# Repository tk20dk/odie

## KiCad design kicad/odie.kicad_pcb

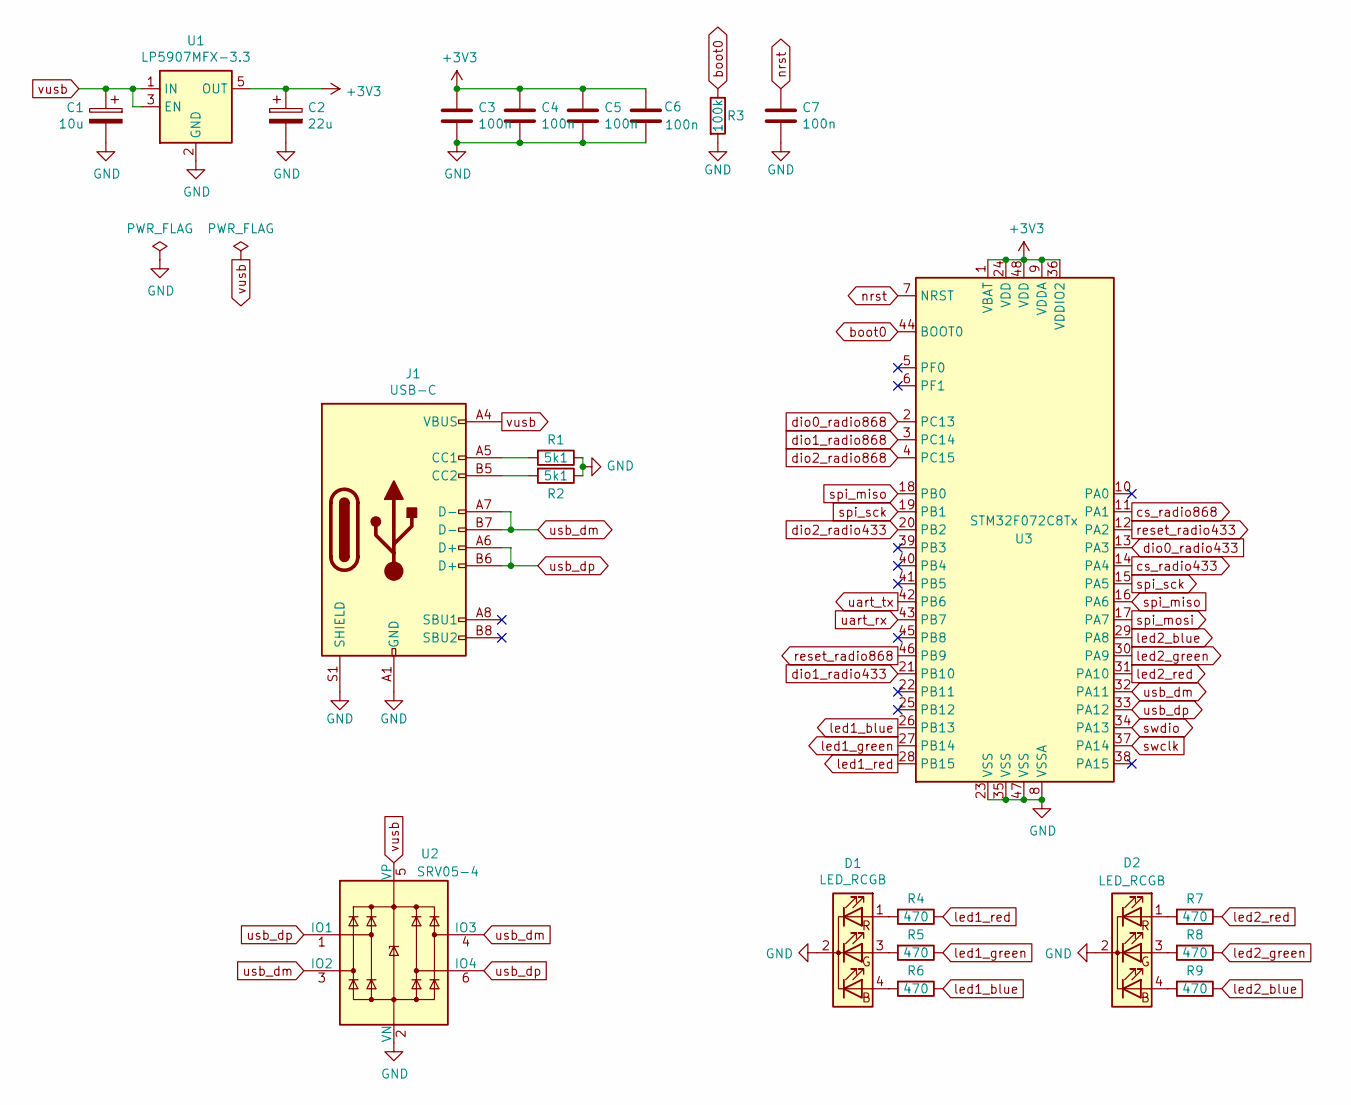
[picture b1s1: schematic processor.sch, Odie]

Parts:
C1: 10u; CP_EIA-3528-12_Kemet-T
C2: 22u; CP_EIA-3528-12_Kemet-T
C3, C4, C5, C6, C7: 100n; C_0603_1608Metric
D1, D2: LED_RCGB; LED_D5.0mm-4
J1: USB-C; USB_C_Receptacle_HRO_TYPE-C-31-M-12
R1, R2: 5k1; R_0603_1608Metric
R3: 100k; R_0603_1608Metric
R4, R5, R6, R7, R8, R9: 470; R_0603_1608Metric
U1: LP5907MFX-3.3; SOT-23-5
U2: SRV05-4; SOT-23-6
U3: STM32F072C8Tx; LQFP-48_7x7mm_P0.5mm

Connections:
GND: C1.2, C2.2, C3.2, C4.2, C5.2, C6.2, C7.2, D1.2 (K), D2.2 (K), J1.A1 (GND), J1.A12 (GND), J1.B1 (GND), J1.B12 (GND), J1.S1 (SHIELD), R1.1, R2.1, R3.2, U1.2 (GND), U2.2 (VN), U3.8 (VSSA), U3.23 (VSS), U3.35 (VSS), U3.47 (VSS); also elsewhere on the board
unnamed: D1.1 (RA), R4.2
unnamed: D1.3 (GA), R5.2
unnamed: D1.4 (BA), R6.2
unnamed: D2.1 (RA), R7.2
unnamed: D2.3 (GA), R8.2
unnamed: D2.4 (BA), R9.2
unnamed: J1.A5 (CC1), R1.2
unnamed: J1.B5 (CC2), R2.2
boot0: R3.1, U3.44 (BOOT0)
cs_radio433: U3.14 (PA4); also elsewhere on the board
cs_radio868: U3.11 (PA1); also elsewhere on the board
dio0_radio433: U3.13 (PA3); also elsewhere on the board
dio0_radio868: U3.2 (PC13); also elsewhere on the board
dio1_radio433: U3.21 (PB10); also elsewhere on the board
dio1_radio868: U3.3 (PC14); also elsewhere on the board
dio2_radio433: U3.20 (PB2); also elsewhere on the board
dio2_radio868: U3.4 (PC15); also elsewhere on the board
led1_blue: R6.1, U3.26 (PB13)
led1_green: R5.1, U3.27 (PB14)
led1_red: R4.1, U3.28 (PB15)
led2_blue: R9.1, U3.29 (PA8)
led2_green: R8.1, U3.30 (PA9)
led2_red: R7.1, U3.31 (PA10)
nrst: C7.1, U3.7 (NRST)
reset_radio433: U3.12 (PA2); also elsewhere on the board
reset_radio868: U3.46 (PB9); also elsewhere on the board
spi_miso: U3.16 (PA6), U3.18 (PB0); also elsewhere on the board
spi_mosi: U3.17 (PA7); also elsewhere on the board
spi_sck: U3.15 (PA5), U3.19 (PB1); also elsewhere on the board
swclk: U3.37 (PA14); also elsewhere on the board
swdio: U3.34 (PA13); also elsewhere on the board
uart_rx: U3.43 (PB7); also elsewhere on the board
uart_tx: U3.42 (PB6); also elsewhere on the board
usb_dm: J1.A7 (D-), J1.B7 (D-), U2.3 (IO2), U2.4 (IO3), U3.32 (PA11)
usb_dp: J1.A6 (D+), J1.B6 (D+), U2.1 (IO1), U2.6 (IO4), U3.33 (PA12)
vusb: C1.1, J1.A4 (VBUS), J1.A9 (VBUS), J1.B4 (VBUS), J1.B9 (VBUS), U1.1 (IN), U1.3 (EN), U2.5 (VP)

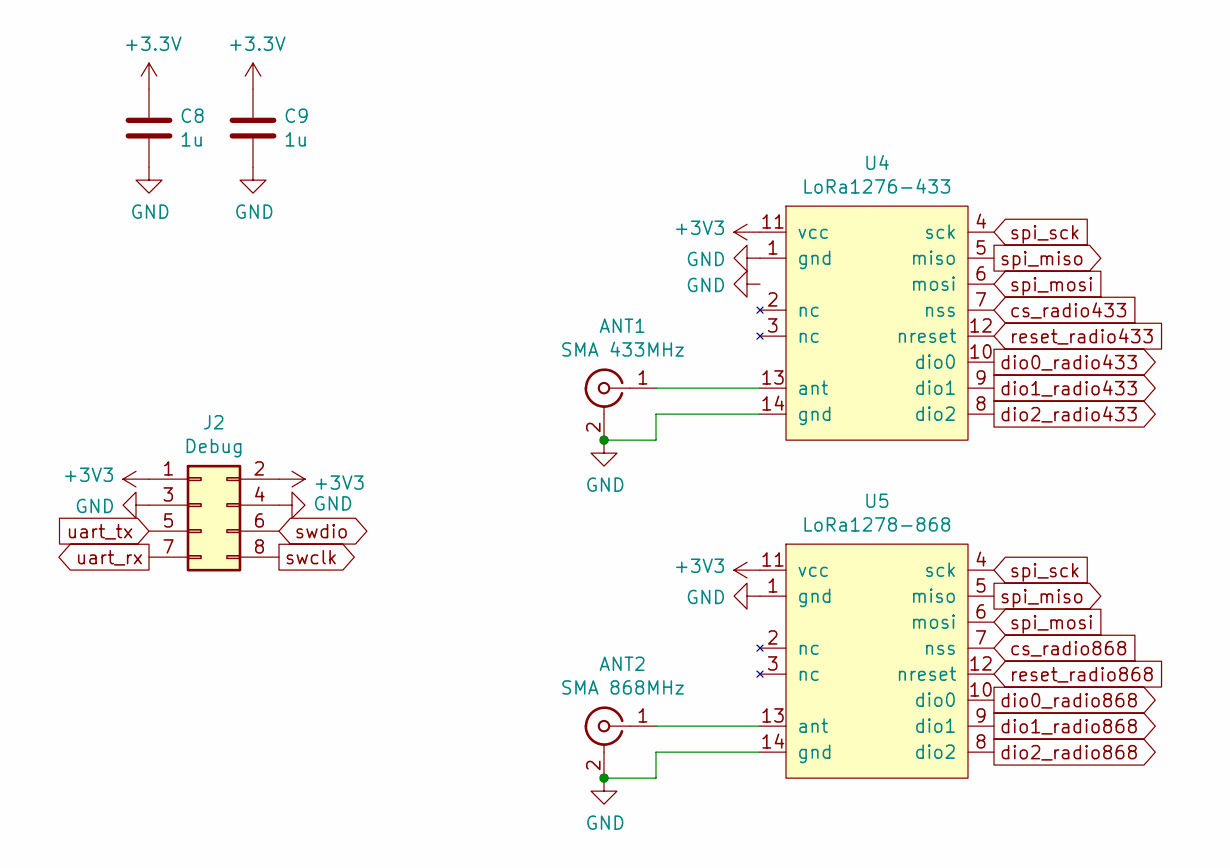
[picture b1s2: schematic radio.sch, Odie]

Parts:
ANT1: SMA 433MHz; SMA_Molex_73251-2200_Horizontal
ANT2: SMA 868MHz; SMA_Molex_73251-2200_Horizontal
C8, C9: 1u; C_0805_2012Metric
J2: Debug; PinHeader_2x04_P2.54mm_Vertical
U4: LoRa1276-433; NicerRF-LoRa1276
U5: LoRa1278-868; NicerRF-LoRa1276

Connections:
GND: ANT1.2 (Ext), ANT2.2 (Ext), C8.2, C9.2, J2.3, J2.4, U4.1 (gnd), U4.14 (gnd), U5.1 (gnd), U5.14 (gnd); also elsewhere on the board
unnamed: ANT1.1 (In), U4.13 (ant)
unnamed: ANT2.1 (In), U5.13 (ant)
cs_radio433: U4.7 (nss); also elsewhere on the board
cs_radio868: U5.7 (nss); also elsewhere on the board
dio0_radio433: U4.10 (dio0); also elsewhere on the board
dio0_radio868: U5.10 (dio0); also elsewhere on the board
dio1_radio433: U4.9 (dio1); also elsewhere on the board
dio1_radio868: U5.9 (dio1); also elsewhere on the board
dio2_radio433: U4.8 (dio2); also elsewhere on the board
dio2_radio868: U5.8 (dio2); also elsewhere on the board
reset_radio433: U4.12 (nreset); also elsewhere on the board
reset_radio868: U5.12 (nreset); also elsewhere on the board
spi_miso: U4.5 (miso), U5.5 (miso); also elsewhere on the board
spi_mosi: U4.6 (mosi), U5.6 (mosi); also elsewhere on the board
spi_sck: U4.4 (sck), U5.4 (sck); also elsewhere on the board
swclk: J2.8; also elsewhere on the board
swdio: J2.6; also elsewhere on the board
uart_rx: J2.7; also elsewhere on the board
uart_tx: J2.5; also elsewhere on the board

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
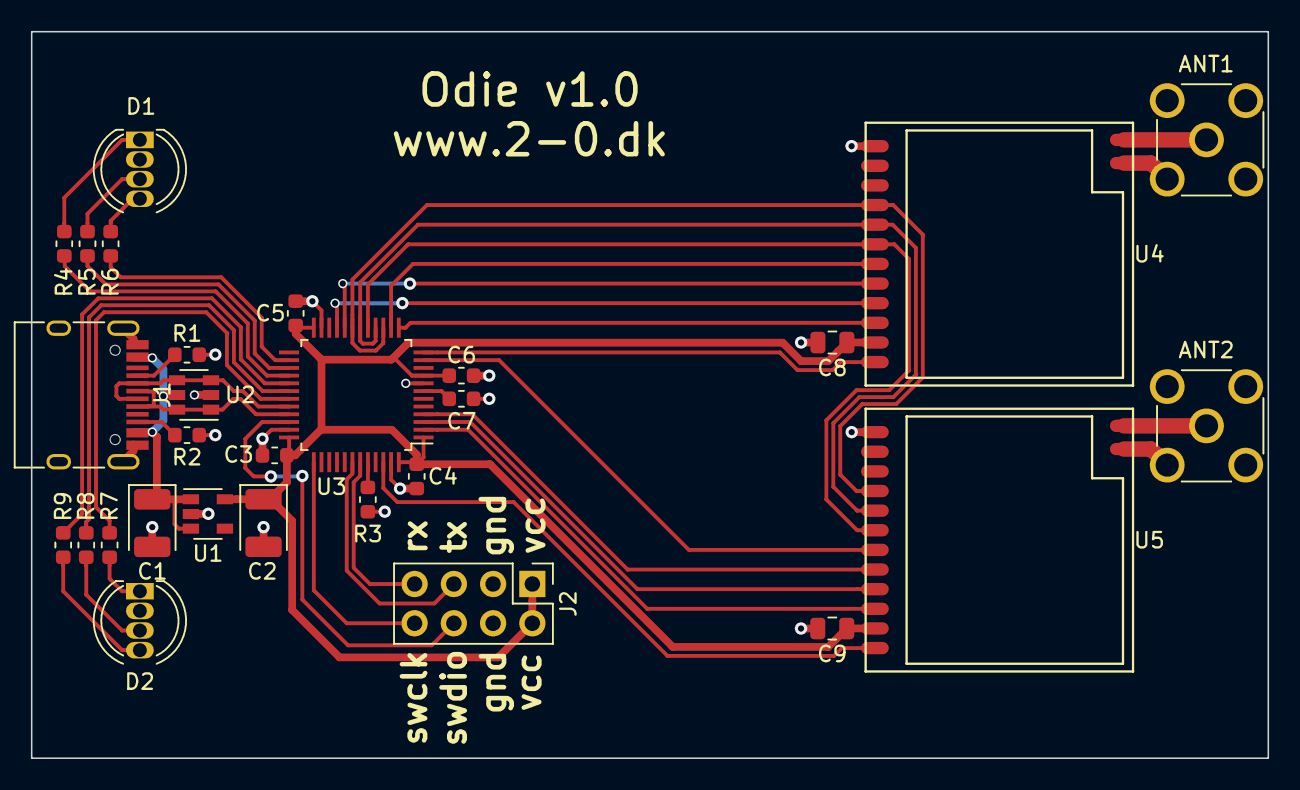
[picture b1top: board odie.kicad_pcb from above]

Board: 2 copper layers, 80.0 x 47.0 mm, 29 parts (0 on the bottom side), 40 nets.

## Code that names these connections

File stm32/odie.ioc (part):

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Mcu.Name=STM32F072C(8-B)Tx
Mcu.Package=LQFP48
Mcu.UserName=STM32F072C8Tx
PA1.GPIOParameters=PinState,GPIO_Label
PA1.GPIO_Label=CS_RADIO868
PA1.PinState=GPIO_PIN_SET
PA1.Signal=GPIO_Output
PA10.GPIOParameters=GPIO_Label
PA10.GPIO_Label=LED2_RED
PA10.Signal=GPIO_Output
PA11.Mode=Device
PA11.Signal=USB_DM
PA12.Mode=Device
PA12.Signal=USB_DP
PA13.Mode=Serial_Wire
PA13.Signal=SYS_SWDIO
PA14.Mode=Serial_Wire
PA14.Signal=SYS_SWCLK
PA2.GPIOParameters=PinState,GPIO_Label
PA2.GPIO_Label=RESET_RADIO433
PA2.PinState=GPIO_PIN_SET
PA2.Signal=GPIO_Output
PA3.GPIOParameters=GPIO_PuPd,GPIO_Label
PA3.GPIO_Label=DIO0_RADIO433
PA3.GPIO_PuPd=GPIO_PULLDOWN
PA3.Signal=GPXTI3
PA4.GPIOParameters=PinState,GPIO_Label
PA4.GPIO_Label=CS_RADIO433
PA4.PinState=GPIO_PIN_SET
PA4.Signal=GPIO_Output
PA5.Mode=Full_Duplex_Master
PA5.Signal=SPI1_SCK
PA6.GPIOParameters=GPIO_PuPd
PA6.GPIO_PuPd=GPIO_PULLUP
PA6.Mode=Full_Duplex_Master
PA6.Signal=SPI1_MISO
PA7.Mode=Full_Duplex_Master
PA7.Signal=SPI1_MOSI
PA8.GPIOParameters=GPIO_Label
PA8.GPIO_Label=LED2_BLUE
PA8.Signal=GPIO_Output
PA9.GPIOParameters=GPIO_Label
PA9.GPIO_Label=LED2_GREEN
PA9.Signal=GPIO_Output
PB0.GPIOParameters=GPIO_Label
PB0.GPIO_Label=SPI_MISO
PB0.Signal=GPIO_Input
PB1.GPIOParameters=GPIO_Label
PB1.GPIO_Label=SPI_SCK
PB1.Signal=GPIO_Input
PB10.GPIOParameters=GPIO_PuPd,GPIO_Label
PB10.GPIO_Label=DIO1_RADIO433
PB10.GPIO_PuPd=GPIO_PULLDOWN
PB10.Signal=GPXTI10
PB13.GPIOParameters=GPIO_Label
PB13.GPIO_Label=LED1_BLUE
PB13.Signal=GPIO_Output
PB14.GPIOParameters=GPIO_Label
PB14.GPIO_Label=LED1_GREEN
PB14.Signal=GPIO_Output
PB15.GPIOParameters=GPIO_Label
PB15.GPIO_Label=LED1_RED
PB15.Signal=GPIO_Output
PB2.GPIOParameters=GPIO_PuPd,GPIO_Label
PB2.GPIO_Label=DIO2_RADIO433
PB2.GPIO_PuPd=GPIO_PULLDOWN
PB2.Signal=GPXTI2
PB6.Mode=Asynchronous
PB6.Signal=USART1_TX
PB7.GPIOParameters=GPIO_PuPd
PB7.GPIO_PuPd=GPIO_PULLUP
PB7.Mode=Asynchronous
PB7.Signal=USART1_RX
PB9.GPIOParameters=PinState,GPIO_Label
PB9.GPIO_Label=RESET_RADIO868
PB9.PinState=GPIO_PIN_SET
PB9.Signal=GPIO_Output
PC13.GPIOParameters=GPIO_PuPd,GPIO_Label
PC13.GPIO_Label=DIO0_RADIO868
PC13.GPIO_PuPd=GPIO_PULLDOWN
PC13.Signal=GPXTI13
PC14-OSC32_IN.GPIOParameters=GPIO_PuPd,GPIO_Label
PC14-OSC32_IN.GPIO_Label=DIO1_RADIO868
PC14-OSC32_IN.GPIO_PuPd=GPIO_PULLDOWN
PC14-OSC32_IN.Signal=GPXTI14
PC15-OSC32_OUT.GPIOParameters=GPIO_PuPd,GPIO_Label
PC15-OSC32_OUT.GPIO_Label=DIO2_RADIO868
PC15-OSC32_OUT.GPIO_PuPd=GPIO_PULLDOWN
PC15-OSC32_OUT.Signal=GPXTI15
RCC.SYSCLKFreq_VALUE=48000000
RCC.SYSCLKSource=RCC_SYSCLKSOURCE_HSI48
board=custom

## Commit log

2020-11-19 created initial kicad and stm32 projects
